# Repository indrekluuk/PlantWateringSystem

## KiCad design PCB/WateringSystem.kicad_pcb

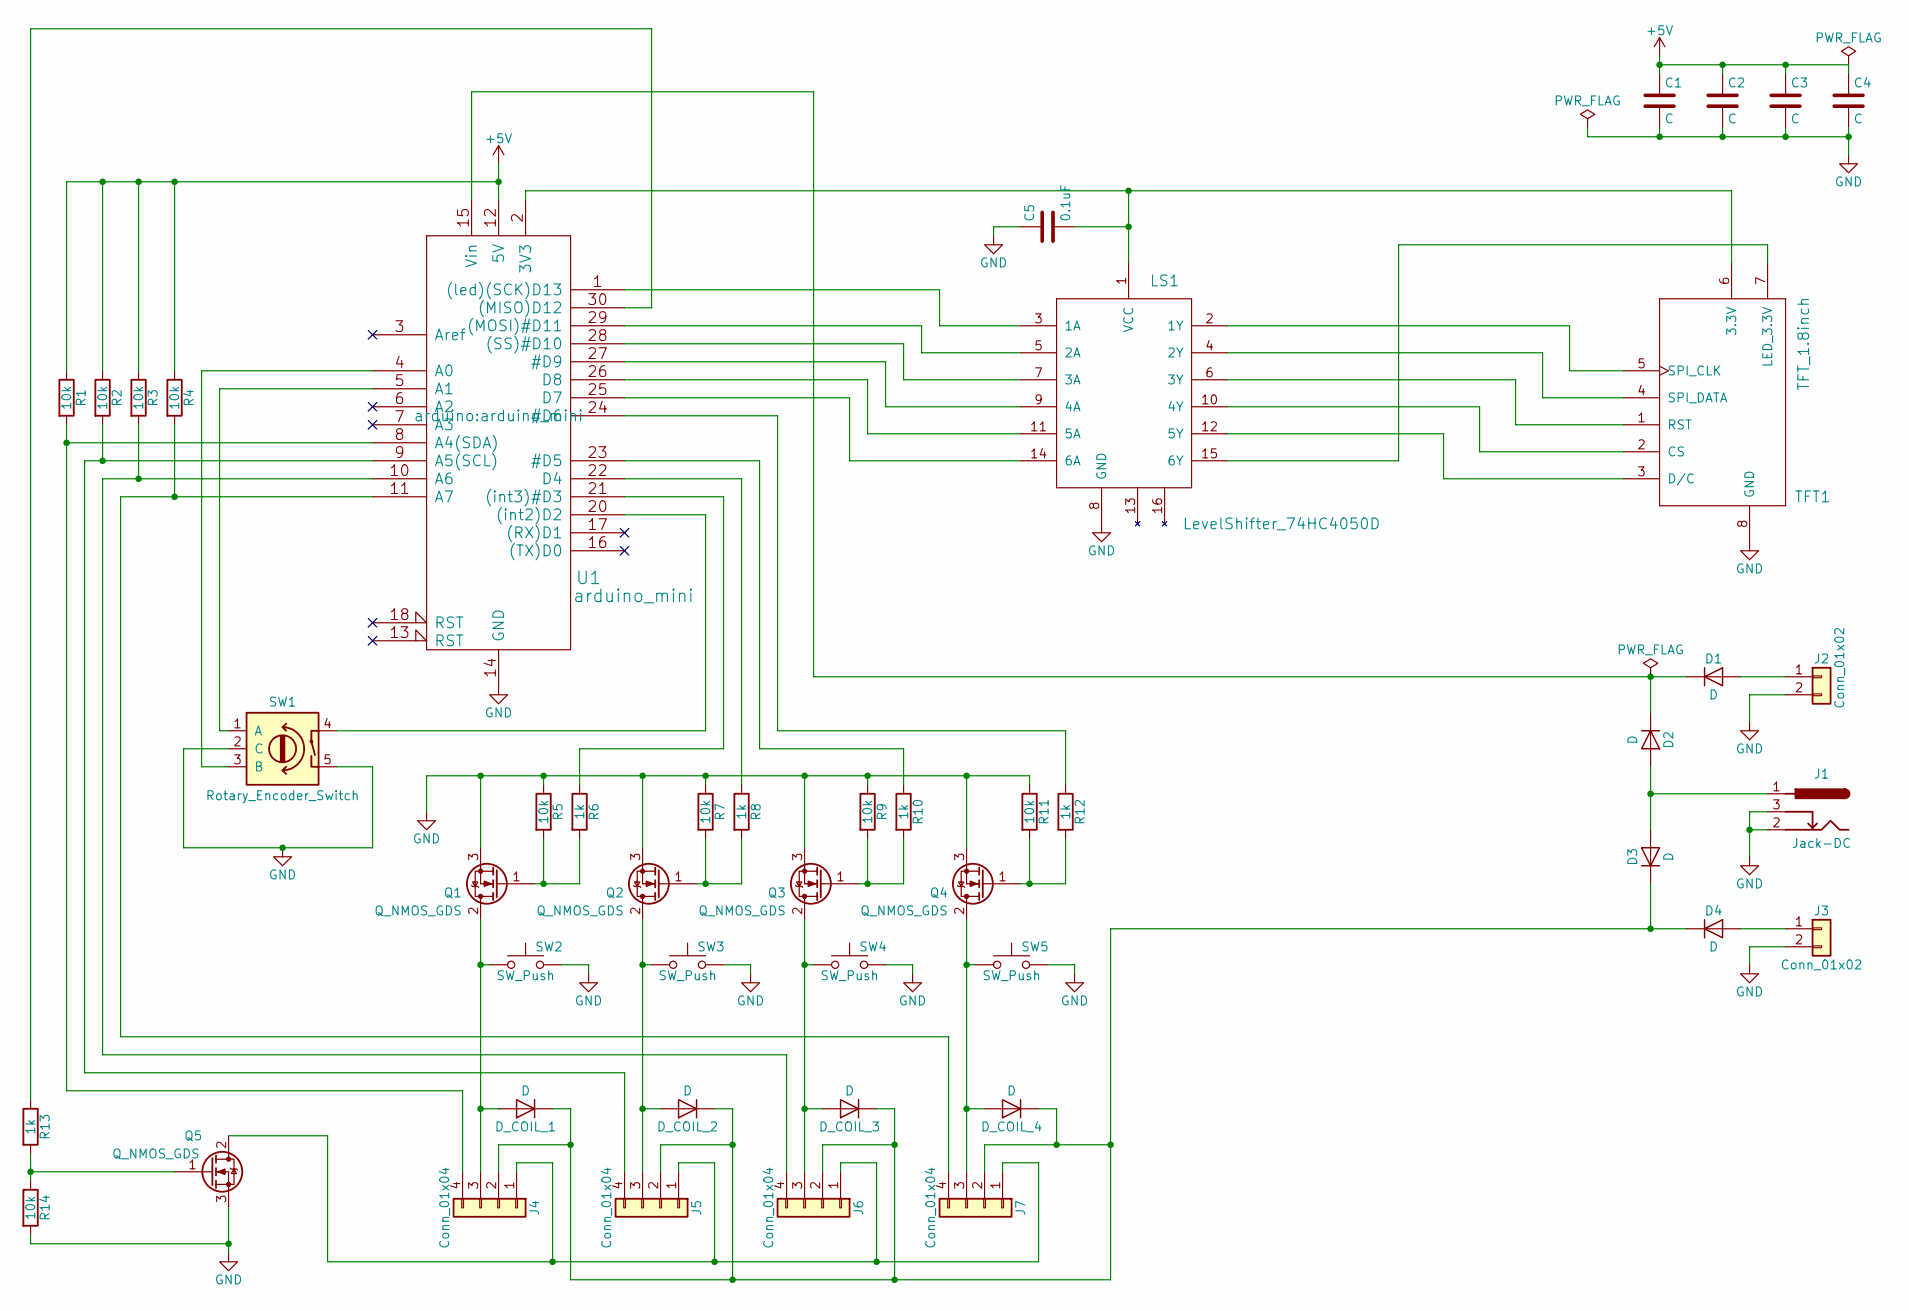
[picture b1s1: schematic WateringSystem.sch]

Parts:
C1, C2: C; C_1206_HandSoldering
C3, C4: C; C_Radial_D5_L6_P2.5
C5: 0.1uF; C_1206_HandSoldering
D1, D2, D3, D4: D; Diode_TO-247_Vertical
D_COIL_1, D_COIL_2, D_COIL_3, D_COIL_4: D; Diode_DO-35_SOD27_Horizontal_RM10
J1: Jack-DC; BARREL_JACK
J2, J3: Conn_01x02; Pin_Header_Straight_1x02
J4, J5, J6, J7: Conn_01x04; Pin_Header_Straight_1x04
LS1: LevelShifter_74HC4050D; SOP-16_4.4x10.4mm_Pitch1.27mm
Q1, Q2, Q3, Q4, Q5: Q_NMOS_GDS; TO-220_Vertical
R1, R2, R3, R4, R5, R7, R9, R11, R14: 10k; R_1206_HandSoldering
R6, R8, R10, R12, R13: 1k; R_1206_HandSoldering
SW1: Rotary_Encoder_Switch; RotaryEncoder
SW2, SW3, SW4, SW5: SW_Push; SW_PUSH_6mm_h5mm
TFT1: TFT_1.8inch; Pin_Header_Straight_1x08
U1: arduino_mini

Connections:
+5V: C1.1, C2.1, C3.1, C4.1, R1.1, R2.1, R3.1, R4.1, U1.12 (5V)
GND: C1.2, C2.2, C3.2, C4.2, C5.1, J1.2, J1.3, J2.2, J3.2, LS1.8 (GND), Q1.3 (S), Q2.3 (S), Q3.3 (S), Q4.3 (S), Q5.3 (S), R5.1, R7.1, R9.1, R11.1, R14.2, SW1.2 (C), SW1.5, SW2.2, SW3.2, SW4.2, SW5.2, TFT1.8 (GND), U1.14 (GND), U1.19 (GND)
unnamed: C5.2, LS1.1 (VCC), TFT1.6 (3.3V), U1.2 (3V3)
unnamed: D1.1 (K), D2.1 (K), U1.15 (Vin)
unnamed: D1.2 (A), J2.1
unnamed: D2.2 (A), D3.2 (A), J1.1
unnamed: D3.1 (K), D4.1 (K), D_COIL_1.1 (K), D_COIL_2.1 (K), D_COIL_3.1 (K), D_COIL_4.1 (K), J4.2, J5.2, J6.2, J7.2
unnamed: D4.2 (A), J3.1
unnamed: D_COIL_1.2 (A), J4.3, Q1.2 (D), SW2.1
unnamed: D_COIL_2.2 (A), J5.3, Q2.2 (D), SW3.1
unnamed: D_COIL_3.2 (A), J6.3, Q3.2 (D), SW4.1
unnamed: D_COIL_4.2 (A), J7.3, Q4.2 (D), SW5.1
unnamed: J4.1, J5.1, J6.1, J7.1, Q5.2 (D)
unnamed: J4.4, R1.2, U1.8 (A4(SDA))
unnamed: J5.4, R2.2, U1.9 (A5(SCL))
unnamed: J6.4, R3.2, U1.10 (A6)
unnamed: J7.4, R4.2, U1.11 (A7)
unnamed: LS1.2 (1Y), TFT1.5 (SPI_CLK)
unnamed: LS1.3 (1A), U1.1 ((led)(SCK)D13)
unnamed: LS1.4 (2Y), TFT1.4 (SPI_DATA)
unnamed: LS1.5 (2A), U1.29 ((MOSI)#D11)
unnamed: LS1.6 (3Y), TFT1.1 (RST)
unnamed: LS1.7 (3A), U1.28 ((SS)#D10)
unnamed: LS1.9 (4A), U1.27 (#D9)
unnamed: LS1.10 (4Y), TFT1.2 (CS)
unnamed: LS1.11 (5A), U1.26 (D8)
unnamed: LS1.12 (5Y), TFT1.3 (D/C)
unnamed: LS1.14 (6A), U1.25 (D7)
unnamed: LS1.15 (6Y), TFT1.7 (LED_3.3V)
unnamed: Q1.1 (G), R5.2, R6.2
unnamed: Q2.1 (G), R7.2, R8.2
unnamed: Q3.1 (G), R9.2, R10.2
unnamed: Q4.1 (G), R11.2, R12.2
unnamed: Q5.1 (G), R13.2, R14.1
unnamed: R6.1, U1.21 ((int3)#D3)
unnamed: R8.1, U1.22 (D4)
unnamed: R10.1, U1.23 (#D5)
unnamed: R12.1, U1.24 (#D6)
unnamed: R13.1, U1.30 ((MISO)D12)
unnamed: SW1.1 (A), U1.5 (A1)
unnamed: SW1.3 (B), U1.4 (A0)
unnamed: SW1.4, U1.20 ((int2)D2)

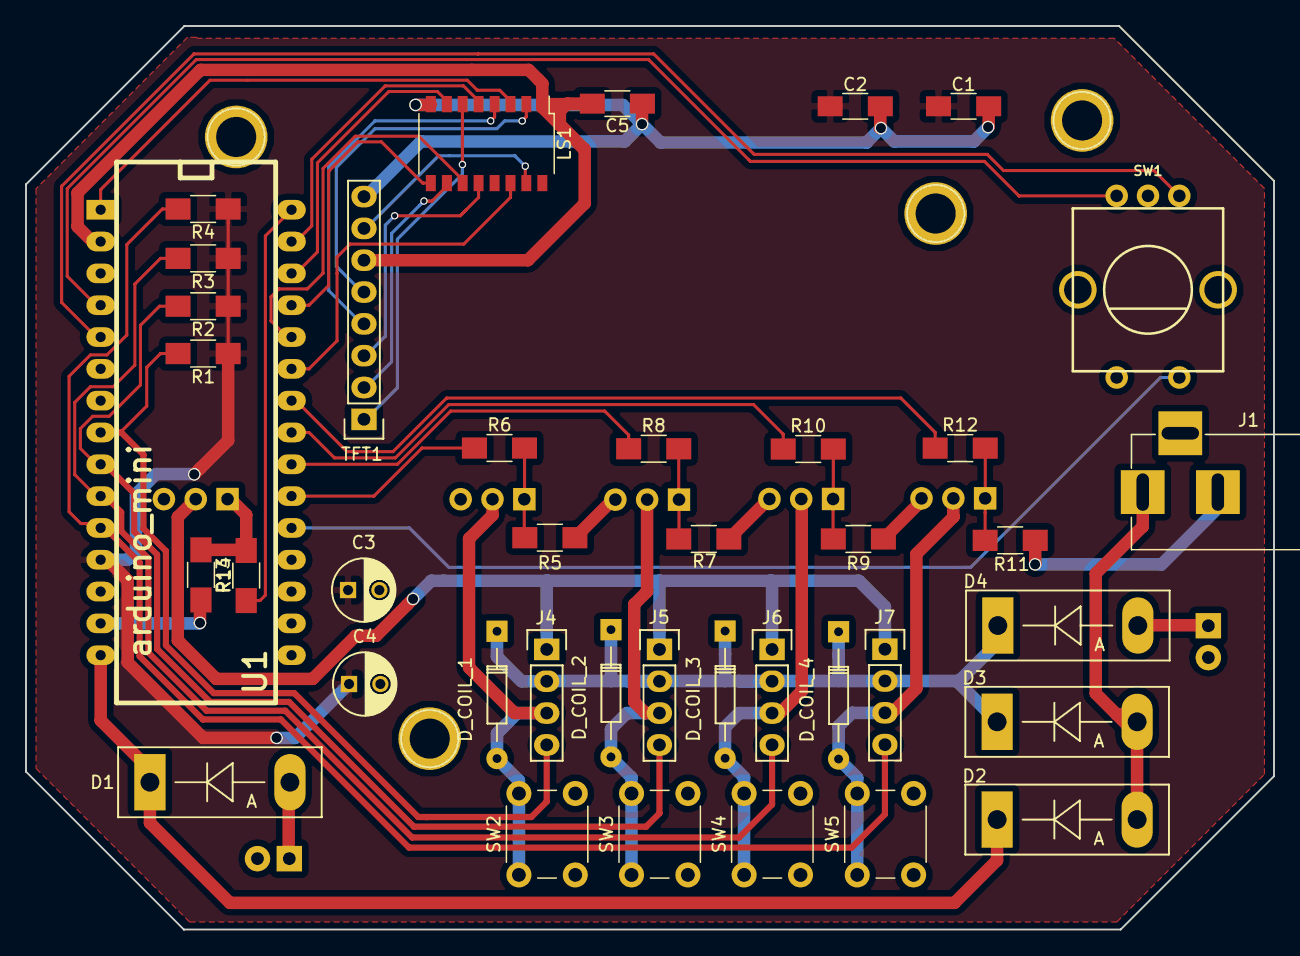
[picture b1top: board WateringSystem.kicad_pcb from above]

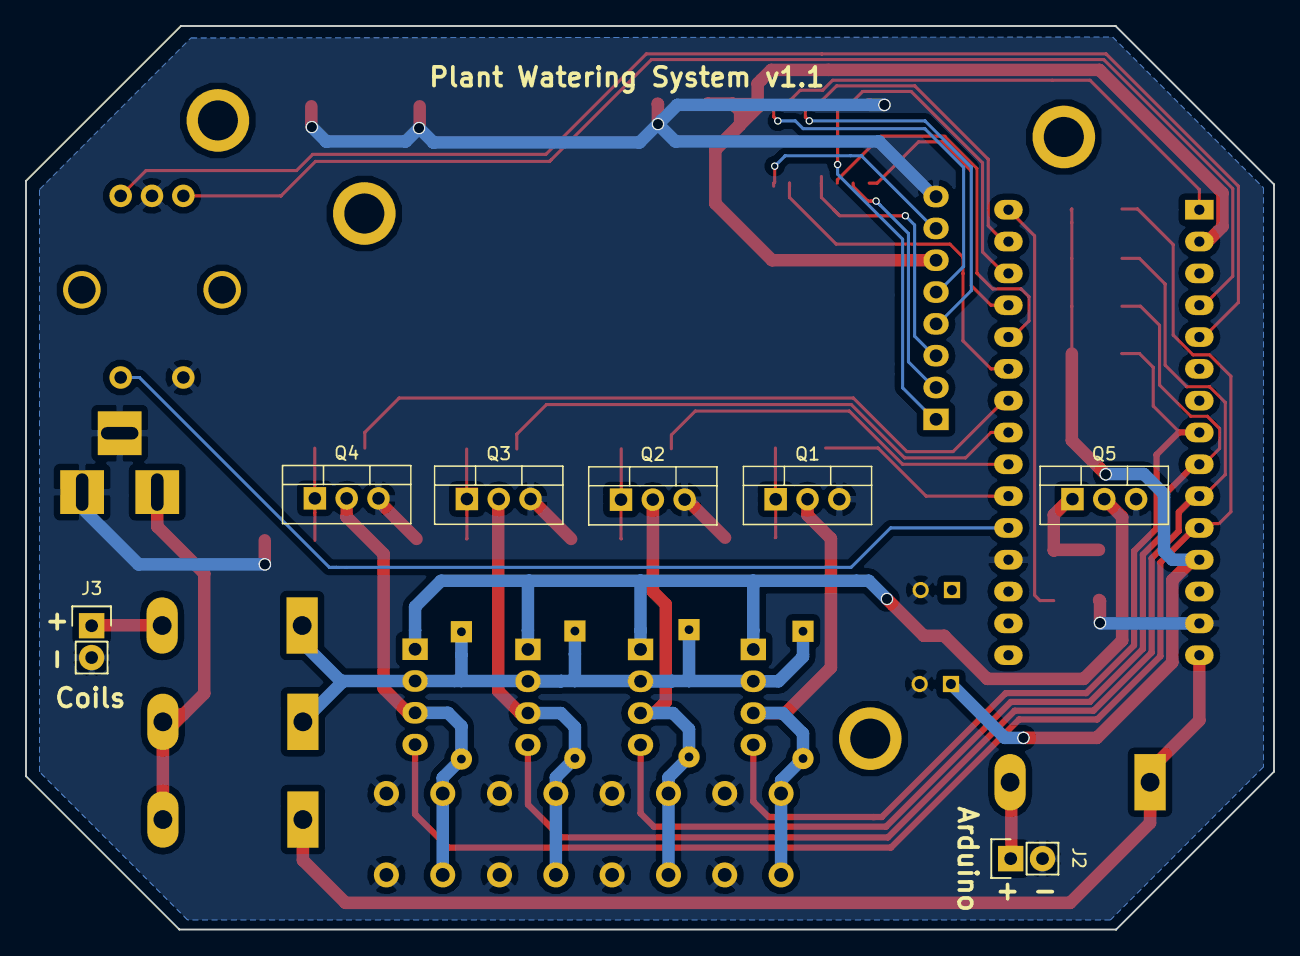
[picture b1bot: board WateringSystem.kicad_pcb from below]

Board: 2 copper layers, 99.6 x 72.1 mm, 47 parts (7 on the bottom side), 42 nets.

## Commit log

2018-05-19 Initial commit. PCB design
2018-05-19 CLion project files
2018-05-19 Added ino file
2018-06-28 fixed screen connector on PCB
2018-06-28 ignore zip file
2018-06-28 button working
2018-06-29 read sensors
2018-06-29 coils
2018-06-29 Consolidated coils and moisture sensor to connector
2018-07-01 fixed and updated PCB
